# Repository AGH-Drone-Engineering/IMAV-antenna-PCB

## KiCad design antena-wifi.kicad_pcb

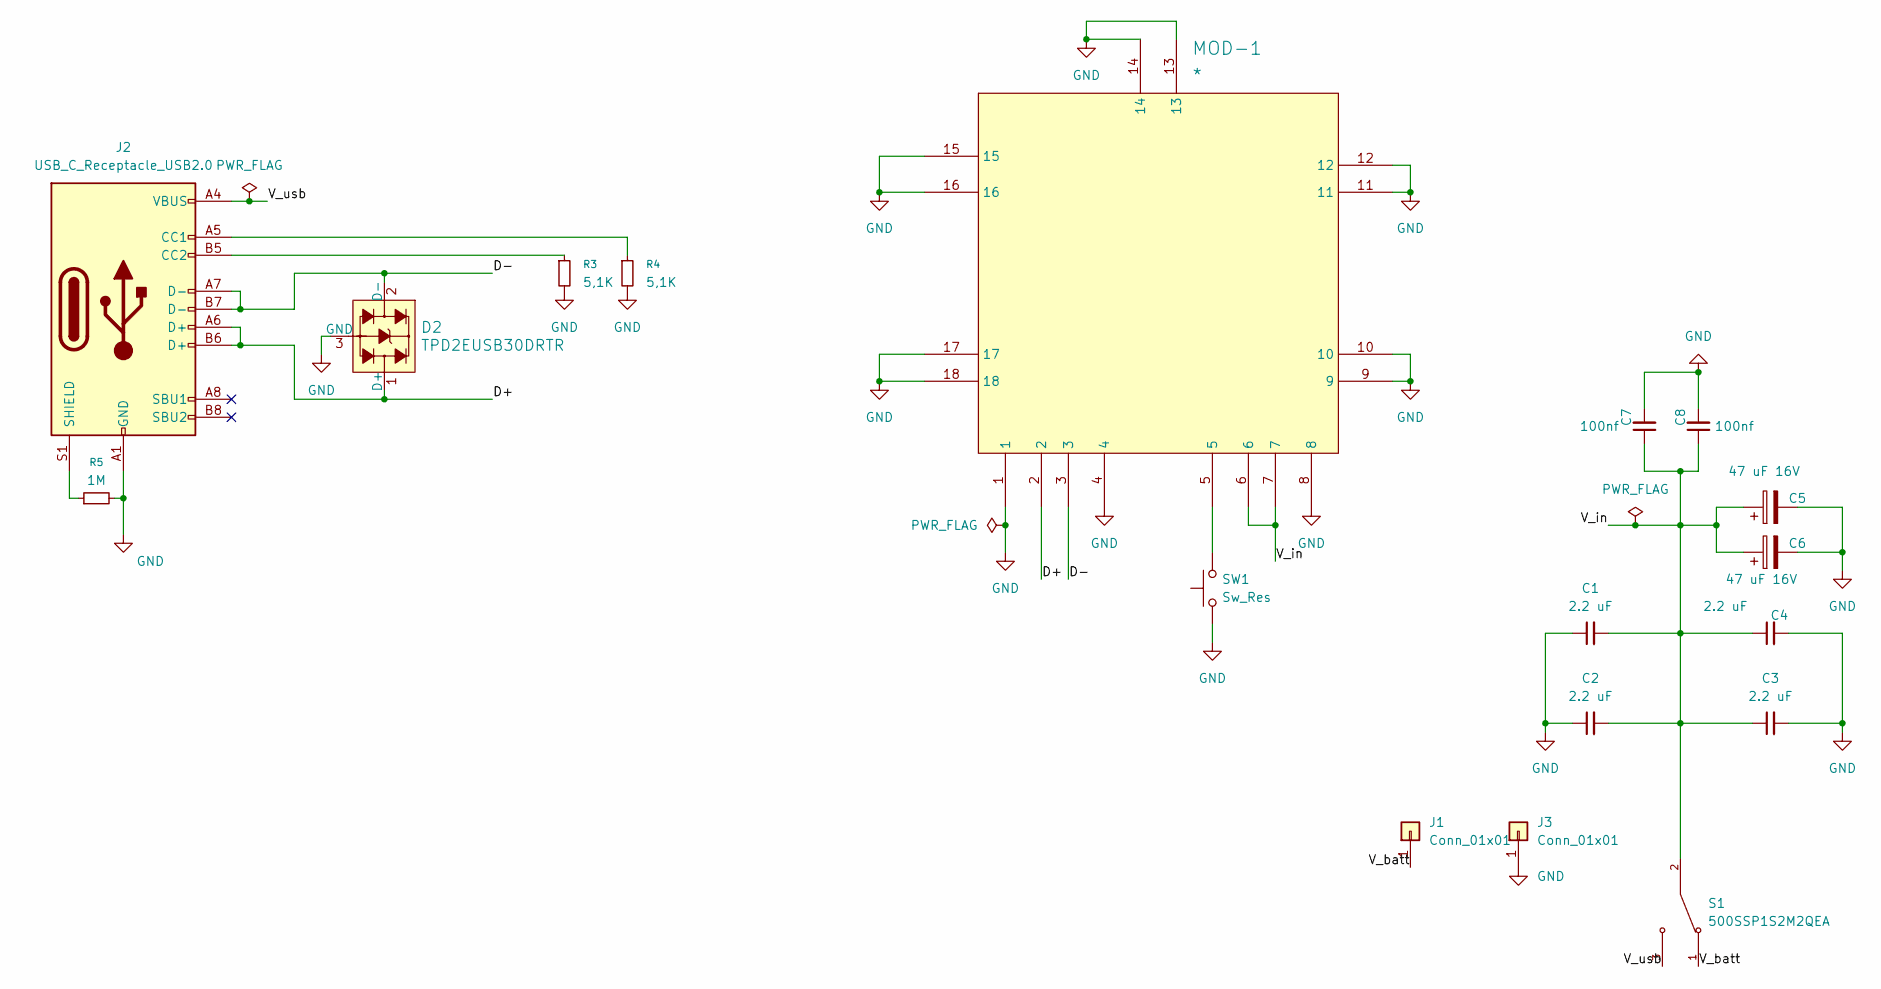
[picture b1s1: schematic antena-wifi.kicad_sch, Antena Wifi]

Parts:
C1, C2, C3, C4: 2.2 uF; CAPC1005X65N
C5, C6: 47 uF 16V; CP_EIA-6032-15_Kemet-U_HandSolder
C7, C8: 100nf; C_0402_1005Metric
D2: TPD2EUSB30DRTR; SOTFL35P100X50-3N; MPN TPD2EUSB30DRTR; Digi-Key_PN 296-25509-1-ND
J1, J3: Conn_01x01; SolderWire-1sqmm_1x01_D1.4mm_OD2.7mm
J2: USB_C_Receptacle_USB2.0; USB_C_Receptacle_GCT_USB4105-xx-A_16P_TopMnt_Horizontal; Part Description USBC USB2 data and power connector
MOD-1: *; BL-M8812EU2
R3, R4: 5,1K; R_0805_2012Metric_Pad1.20x1.40mm_HandSolder
R5: 1M; R_0805_2012Metric_Pad1.20x1.40mm_HandSolder
S1: 500SSP1S2M2QEA; SW_100SP3T1B1M2QEH; PARTREV B
SW1: Sw_Res; SW_Push_1P1T_NO_CK_KMR2

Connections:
/D+: D2.1 (D+), J2.A6 (D+), J2.B6 (D+), MOD-1.2
/D-: D2.2 (D-), J2.A7 (D-), J2.B7 (D-), MOD-1.3
/V_batt: J1.1, S1.1
/V_in: C1.2, C2.2, C3.1, C4.1, C5.1, C6.1, C7.1, C8.1, MOD-1.6, MOD-1.7, S1.2
/V_usb: J2.A4 (VBUS), J2.A9 (VBUS), J2.B4 (VBUS), J2.B9 (VBUS), S1.3
GND: C1.1, C2.1, C3.2, C4.2, C5.2, C6.2, C7.2, C8.2, D2.3 (GND), J2.A1 (GND), J2.A12 (GND), J2.B1 (GND), J2.B12 (GND), J3.1, MOD-1.1, MOD-1.4, MOD-1.8, MOD-1.9, MOD-1.10, MOD-1.11, MOD-1.12, MOD-1.13, MOD-1.14, MOD-1.15, MOD-1.16, MOD-1.17, MOD-1.18, R3.2, R4.2, R5.2, SW1.1; also elsewhere on the board
unnamed: J2.A5 (CC1), R4.1
unnamed: J2.B5 (CC2), R3.1
unnamed: J2.S1 (SHIELD), R5.1
unnamed: MOD-1.5, SW1.2

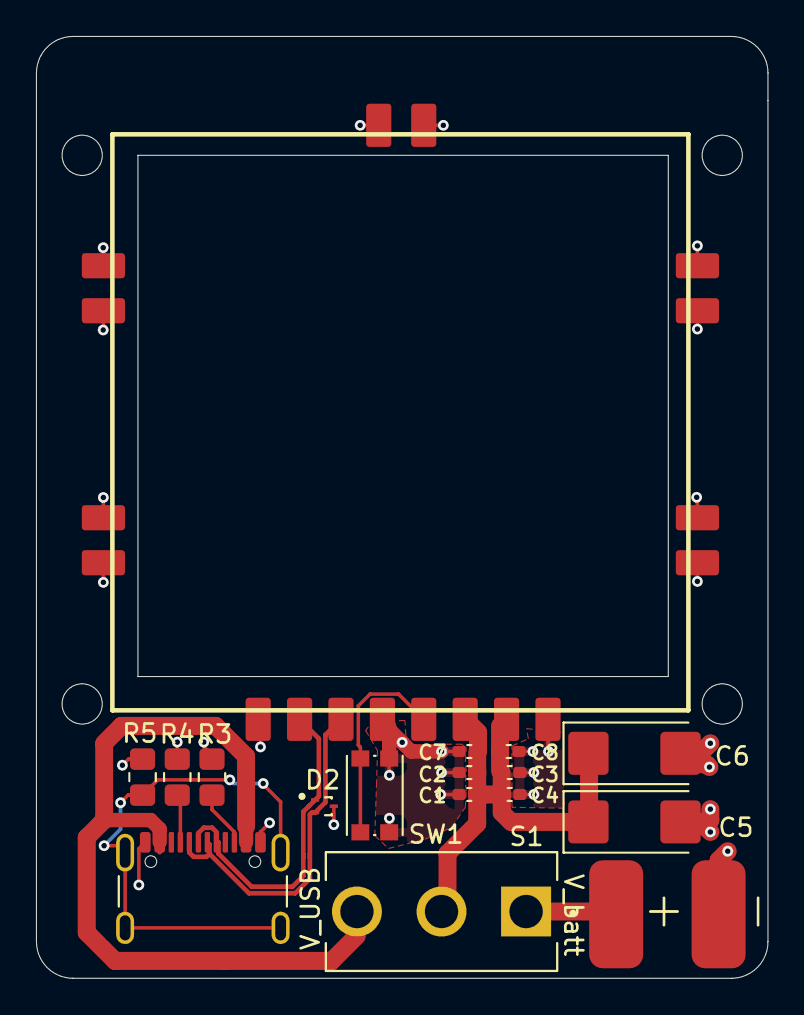
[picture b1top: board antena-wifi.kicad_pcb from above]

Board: 2 copper layers, 40.6 x 52.3 mm, 18 parts (0 on the bottom side), 10 nets.

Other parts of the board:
-: Conn_01x01; SolderWirePad_1x01_SMD_3x6mm

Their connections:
GND: -.1; also elsewhere on the board
